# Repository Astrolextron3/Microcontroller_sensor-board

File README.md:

ATmega328P + BME280 Sensor Breakout Board

📖 Project Overview

This project is a custom-designed microcontroller board based on the ATmega328P, integrated with a BME280 environmental sensor (temperature, humidity, pressure) using the I²C protocol.

The board includes:

On-board clock (crystal oscillator)
Proper power decoupling
ISP programming interface
Clean ERC & DRC-verified PCB layout
3D-validated mechanical design

The goal of this project was to design a production-ready embedded hardware board, following industry best practices.

🧩 Features

ATmega328P (DIP package) microcontroller
BME280 sensor (I²C mode)
External crystal oscillator with load capacitors
Proper AVCC, VCC, and AREF handling
ISP header for programming (AVR-ISP)
Fully ERC & DRC clean design
Compact, single-board solution

⚙️ Hardware Specifications
Component	Description
MCU	ATmega328P
Sensor	Bosch BME280
Interface	I²C
Clock	External crystal
Programming	AVR ISP (SPI)
Supply Voltage	5V
PCB Layers	2-layer

🔌 Pin Configuration (Key Connections)

ATmega328P
VCC / AVCC → 5V (with decoupling capacitors)
AREF → 100nF capacitor to GND
XTAL1 / XTAL2 → External crystal + 22pF caps
RESET → Pull-up resistor (10kΩ)
SPI Pins → Connected to ISP header

BME280 (I²C Mode)

SDI (SDA) → MCU SDA
SCK (SCL) → MCU SCL
CSB → Pulled HIGH (I²C selection)
SDO → GND (I²C address = 0x76)

🛠️ Design Workflow

Schematic design with ERC validation
Footprint assignment & verification
PCB placement with routing optimization
Manual routing (no autorouter)
DRC clean check
3D view validation

🧪 Design Checks

✅ ERC: Clean
✅ DRC: Clean
✅ No unconnected nets
✅ Silkscreen overlap resolved

📷 Project Media

Include the following in your GitHub repo:

📄 Schematic PDF
🧠 PCB layout screenshots
🧊 3D render images
🗂 KiCad project files

🚀 Future Improvements

Ground plane pour for EMI reduction
Test pads for debugging
USB-to-UART onboard
Enclosure-ready board outline

🧑‍💻 Tools Used

KiCad (Schematic, PCB, 3D Viewer)
AVR Architecture
I²C Protocol

📜 License

This project is open-source and intended for learning and demonstration purposes.

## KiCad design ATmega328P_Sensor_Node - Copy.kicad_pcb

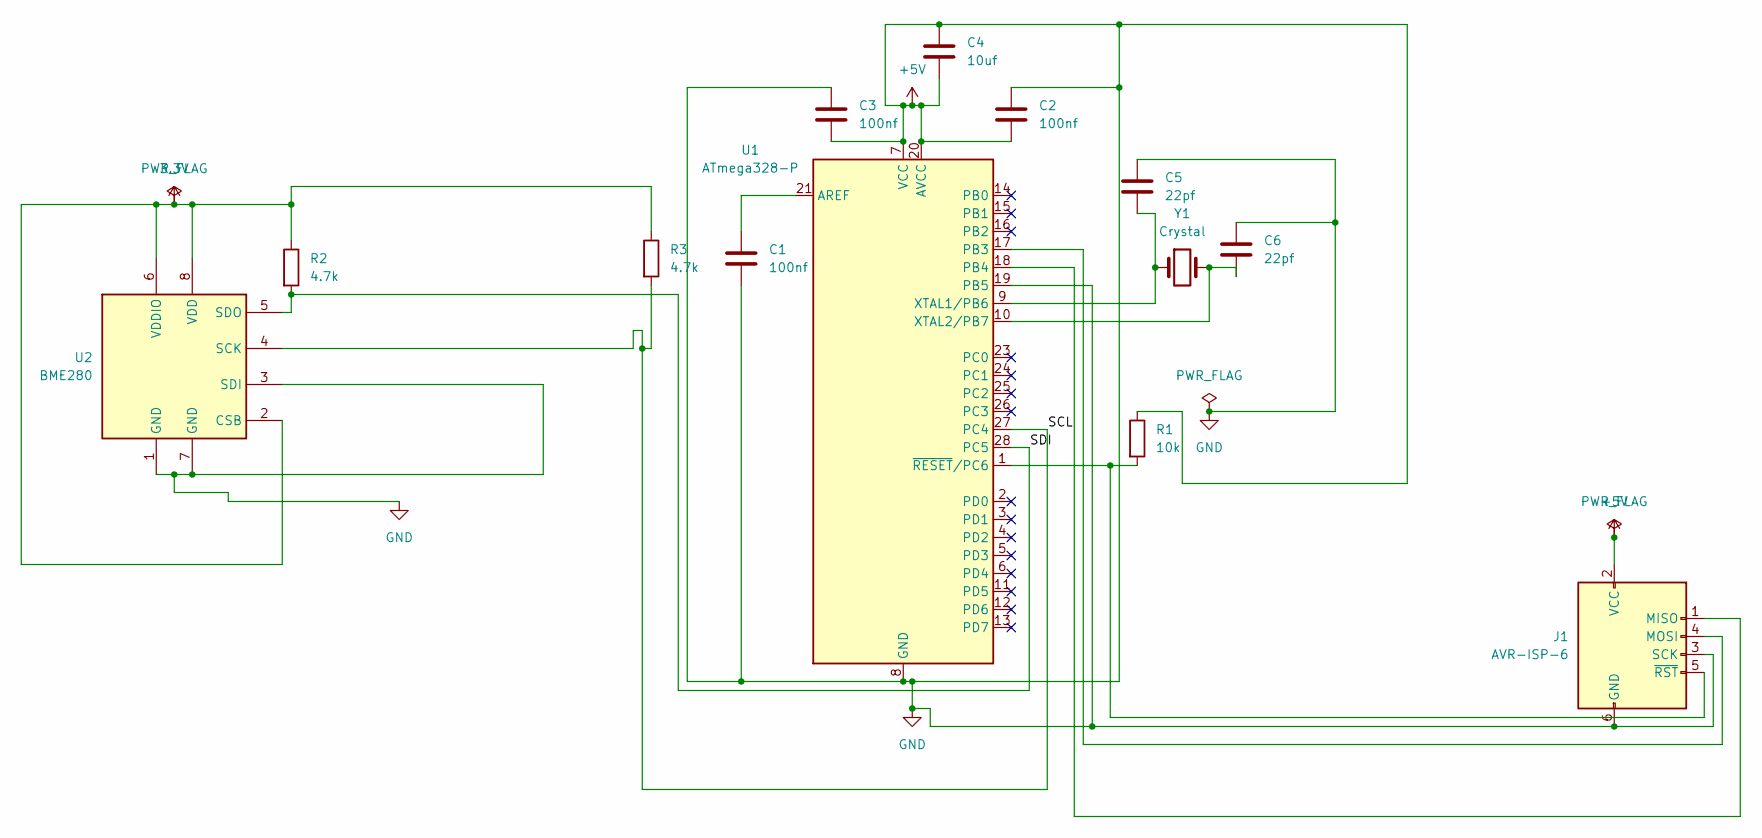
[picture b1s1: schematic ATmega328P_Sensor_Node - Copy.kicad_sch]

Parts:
C1, C2, C3: 100nf; C_0805_2012Metric
C4: 10uf; C_0805_2012Metric
C5, C6: 22pf; C_0805_2012Metric
J1: AVR-ISP-6; PinHeader_2x03_P2.54mm_Vertical
R1: 10k; R_0805_2012Metric
R2, R3: 4.7k; R_0805_2012Metric
U1: ATmega328-P; DIP-28_W7.62mm
U2: BME280; Bosch_LGA-8_2.5x2.5mm_P0.65mm_ClockwisePinNumbering
Y1: Crystal; Crystal_SMD_HC49-SD

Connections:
3.3V: R2.1, R3.1, U2.2 (CSB), U2.6 (VDDIO), U2.8 (VDD)
+5V: C1.2, C2.1, C2.2, C3.1, C3.2, C4.1, C4.2, C5.1, C6.1, J1.2 (VCC), J1.3 (SCK), J1.6 (GND), R1.1, U1.7 (VCC), U1.8 (GND), U1.19 (PB5), U1.20 (AVCC), U1.22 (GND), U2.1 (GND), U2.3 (SDI), U2.7 (GND)
/SCL: R3.2, U1.27 (PC4), U2.4 (SCK)
/SDI: R2.2, U1.28 (PC5), U2.5 (SDO)
unnamed: J1.1 (MISO), U1.18 (PB4)
unnamed: J1.4 (MOSI), U1.17 (PB3)
unnamed: J1.5 (~RST), R1.2, U1.1 (~RESET/PC6)
unnamed: C1.1, U1.21 (AREF)
unnamed: C5.2, U1.9 (XTAL1/PB6), Y1.1
unnamed: C6.2, U1.10 (XTAL2/PB7), Y1.2

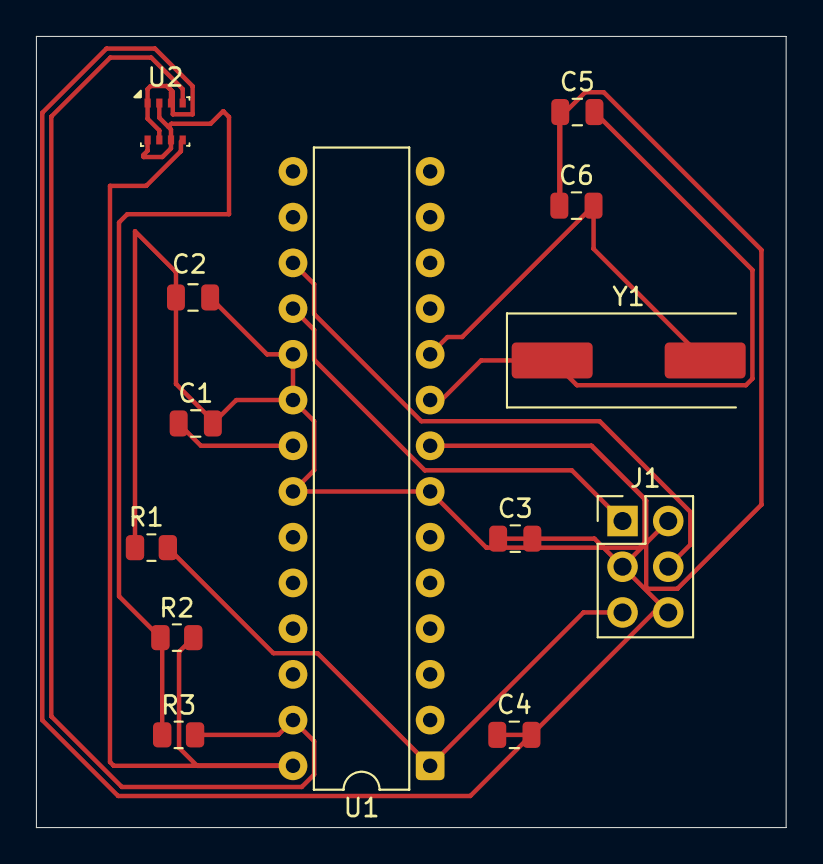
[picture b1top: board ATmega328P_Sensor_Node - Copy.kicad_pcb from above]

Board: 2 copper layers, 41.7 x 43.9 mm, 13 parts (0 on the bottom side), 10 nets.

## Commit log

2026-02-08 Update README with project details and specifications
    Added detailed project overview, features, specifications, and design workflow for the microcontroller sensor board.
